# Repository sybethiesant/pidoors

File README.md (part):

# PiDoors - Open Source Access Control System

**Professional-grade physical access control powered by Raspberry Pi**

---

## Overview

PiDoors is a complete, industrial-grade access control system built on Raspberry Pi hardware. It provides enterprise-level security features while remaining affordable and open source. Designed for small businesses, makerspaces, office buildings, or anyone needing professional access control.

**Key Benefits:**
- **Cost-Effective**: 10x cheaper than commercial systems (~$100-150 per door vs $500-2000)
- **Secure**: TLS database encryption, bcrypt passwords, SQL injection protection, CSRF tokens
- **Open Source**: Full control over your security system
- **Modern Interface**: React SPA with TailwindCSS — fast, responsive single-page application
- **Offline Capable**: 24-hour local caching keeps doors working during network outages
- **Extensible**: Easy to customize and integrate

---

## Screenshots

| Dashboard | Doors |
|-----------|-------|
|  |  |

| Cards | Access Logs |
|-------|-------------|
|  |  |

| Schedules | Access Groups |
|-----------|---------------|
|  |  |

| Reports | Updates |
|---------|---------|
|  |  |

<details>
<summary>More screenshots</summary>

| Door Settings | Card Edit | Audit Log |
|---------------|-----------|-----------|
|  |  |  |

</details>

---

## Features

### Access Control
- **Multi-format Wiegand**: 26, 32, 34, 35, 36, 37, 48-bit with auto-detection
- **OSDP Readers**: RS-485 encrypted readers (planned — reader module included, not yet integrated)
- **NFC/RFID**: PN532 and MFRC522 support (planned — reader modules included, not yet integrated)
- Time-based access schedules
- Scheduled unlock — hold a door or gate open during a schedule's hours (e.g. a community gate open 6am–7pm)
- Access groups and permissions
- Holiday calendar support
- Card validity date ranges
- Persistent master cards (never expire for emergency access)
- **Master card toggle** in web UI — promote any card to master with a checkbox

### Gate Mode
- Toggle any door into **gate mode** for rolling/sliding gates with motor controllers
- 3 configurable inputs (open / stop / close physical buttons)
- 3 configurable outputs (open / stop / close relays to gate motor)
- Per-output hold duration, configurable polarity, configurable GPIO pins
- Triple-tap any button to enter hold-current-state
- Master card 3-scan = hold open (configurable)
- Stop interrupts the active output immediately
- Reverse direction commands automatically stop and reverse
- Web UI shows live gate state (idle/opening/closing/stopped/open/closed) and dedicated control buttons
- State persists across controller restarts
- Server-side pin conflict checker prevents double-assigning GPIO pins

### Reader LED
- Green / on while the door is unlocked or held open (schedule, master card or admin), red / off otherwise; a denied card blinks red
- Per-door green pin, optional red pin for bicolor readers, hi/lo polarity; defaults to the original GPIO 25 / GPIO 22 wiring
- Works on both doors and gates

### Management
- Modern React SPA with REST API backend
- Login by username or email
- Real-time dashboard with analytics
- Multi-user administration with extended profiles (name, department, company, etc.)
- Extended cardholder details (email, phone, department, employee ID, company, title)
- CSV bulk import/export with all cardholder fields (including master card flag)
- Comprehensive reporting
- Email notifications
- Complete audit trail
- Remote door control
- Instant offline detection via server-initiated polling (no stale heartbeat data)
- Door auto-registration from client heartbeat

### Updates
- One-click server updates from the web UI
- Remote controller updates via heartbeat signaling
- Pre-flight checks prevent partial updates
- Actionable error messages on failure
- Version tracking across all doors and server

### Reliability
- 24-hour offline operation
- Automatic failover
- Health monitoring
- Auto-reconnection
- Automated backups
- Service redundancy

### Security
- **TLS database encryption** — controller-to-server connections encrypted automatically
- Bcrypt password hashing (cost 12)
- PDO prepared statements (SQL injection proof)
- CSRF protection on all forms
- Secure session management
- Input validation and sanitization
- Security event logging
- Rate limiting on login

---

## Quick Start

### Prerequisites

- Raspberry Pi 3B+ or newer (Pi 4 recommended for server)
- Raspberry Pi OS (Debian-based, 64-bit recommended)
- Internet connection for initial setup
- Node.js and npm (installed automatically by `install.sh`)
- For door controllers: card reader hardware and relay module

### Automated Installation (Recommended)

```bash
# Download PiDoors
git clone https://github.com/sybethiesant/pidoors.git
cd pidoors

# Run installer as root
sudo ./install.sh
```

The installer presents three installation modes:

| Mode | Use Case |
|------|----------|
| **1) Server** | Web interface + MariaDB database (run on your central Pi) |
| **2) Door Controller** | GPIO + card reader daemon (run on each door Pi) |
| **3) Full** | Both server and controller on one Pi (small deployments) |

#### What the installer does

1. Updates system packages
2. Installs dependencies (Nginx, PHP-FPM, MariaDB, Node.js, Python libraries)
3. Generates TLS certificates and enables encrypted database connections
4. Creates the `users` and `access` databases with all required tables
5. Imports the full database schema (base tables + migration extensions)
6. Deploys the PHP API to `/var/www/pidoors/`
7. Builds the React SPA and deploys to `/var/www/pidoors-ui/`
8. Configures Nginx to serve the SPA with `/api/*` routed to PHP-FPM
9. Prompts you to create an admin account (username, email + password)
10. Sets up log rotation and backup scripts

#### After installation

1. Open `https://your-pi-ip/` in a browser
2. Log in with the email (or username `Admin`) and password you set during install
3. Navigate to **Doors** to see your door controllers as they come online
4. Navigate to **Cards** to add access cards
5. Set up **Schedules** and **Access Groups** as needed

> **Installing a door controller on a separate Pi?** The server install prints a **controller enrollment token** at the end (also stored in `/var/www/pidoors/includes/config.php` as `enrollment_token`). Enter it when the door-controller install asks for it. It lets the controller obtain a CA-signed certificate so the server can push commands to it instantly; without it the controller still works, but commands fall back to database polling.

### Manual Installation

If you prefer to install manually or need to troubleshoot:

#### 1. Install system packages
```bash
sudo apt-get update && sudo apt-get install -y \
  nginx php-fpm php-mysql php-cli php-mbstring php-curl php-json \
  mariadb-server nodejs npm \
  python3 python3-pip python3-dev python3-venv git curl
```

#### 2. Create databases
```bash
sudo mysql_secure_installation

sudo mysql -u root -p <<'SQL'
CREATE DATABASE IF NOT EXISTS users;
CREATE DATABASE IF NOT EXISTS access;
CREATE USER IF NOT EXISTS 'pidoors'@'localhost' IDENTIFIED BY 'YOUR_PASSWORD';
CREATE USER IF NOT EXISTS 'pidoors'@'%' IDENTIFIED BY 'YOUR_PASSWORD';
GRANT ALL PRIVILEGES ON users.* TO 'pidoors'@'localhost';
GRANT ALL PRIVILEGES ON access.* TO 'pidoors'@'localhost';
GRANT ALL PRIVILEGES ON users.* TO 'pidoors'@'%';
GRANT ALL PRIVILEGES ON access.* TO 'pidoors'@'%';
FLUSH PRIVILEGES;
SQL
```

> **Note:** The `'pidoors'@'%'` user allows door controllers on other Pis to connect remotely. You also need to set `bind-address = 0.0.0.0` in `/etc/mysql/mariadb.conf.d/50-server.cnf` and restart MariaDB.

#### 3. Import schemas
```bash
# Create the users table and audit_logs table in the users database
sudo mysql -u root -p users <<'SQL'
CREATE TABLE IF NOT EXISTS `users` (
  `id` int(11) NOT NULL AUTO_INCREMENT,
  `user_name` varchar(100) NOT NULL,
  `user_email` varchar(255) NOT NULL,
  `user_pass` varchar(255) NOT NULL,
  `admin` tinyint(1) NOT NULL DEFAULT 0,
  `active` tinyint(1) NOT NULL DEFAULT 1,
  `created_at` datetime DEFAULT CURRENT_TIMESTAMP,
  `last_login` datetime DEFAULT NULL,
  PRIMARY KEY (`id`),
  UNIQUE KEY `user_email` (`user_email`)
) ENGINE=InnoDB DEFAULT CHARSET=utf8mb4;

CREATE TABLE IF NOT EXISTS `audit_logs` (
  `id` int(11) NOT NULL AUTO_INCREMENT,
  `event_type` varchar(50) NOT NULL,
  `user_id` int(11) DEFAULT NULL,
  `ip_address` varchar(45) DEFAULT NULL,
  `user_agent` varchar(255) DEFAULT NULL,
  `details` text,
  `created_at` datetime NOT NULL DEFAULT CURRENT_TIMESTAMP,
  PRIMARY KEY (`id`),
  KEY `event_type` (`event_type`),
  KEY `user_id` (`user_id`),
  KEY `created_at` (`created_at`)
) ENGINE=InnoDB DEFAULT CHARSET=utf8mb4;
SQL

# Import the access database schema and migration extensions
sudo mysql -u root -p access < database_migration.sql
```

The migration script creates all access tables, adds extended columns, and also switches to the `users` database to add profile columns. It is safe to re-run on existing installations.

#### 4. Create your admin user
```bash
# Generate a bcrypt hash for your password
HASH=$(php -r "echo password_hash('YOUR_PASSWORD', PASSWORD_BCRYPT);")

sudo mysql -u root -p users -e \
  "INSERT INTO users (user_name, user_email, user_pass, admin, active) \
   VALUES ('Admin', 'admin@example.com', '$HASH', 1, 1);"
```

#### 5. Deploy the PHP API
```bash
sudo mkdir -p /var/www/pidoors
sudo cp -r pidoorserv/* /var/www/pidoors/
sudo cp VERSION /var/www/pidoors/
sudo cp /var/www/pidoors/includes/config.php.example /var/www/pidoors/includes/config.php
sudo nano /var/www/pidoors/includes/config.php    # Set your database password and server IP
sudo chown -R www-data:www-data /var/www/pidoors
sudo chmod 640 /var/www/pidoors/includes/config.php
```

#### 6. Build and deploy the React SPA
```bash
sudo apt-get install -y nodejs npm
cd pidoors-ui
npm install && npm run build
sudo mkdir -p /var/www/pidoors-ui
sudo cp -r dist/* /var/www/pidoors-ui/
sudo chown -R www-data:www-data /var/www/pidoors-ui
cd ..
```

#### 7. Configure Nginx
```bash
# Detect your PHP version
PHP_VERSION=$(php -r "echo PHP_MAJOR_VERSION.'.'.PHP_MINOR_VERSION;")

# Install config with correct PHP socket path
sudo sed "s|php-fpm.sock|php${PHP_VERSION}-fpm.sock|g" \
  nginx/pidoors.conf > /etc/nginx/sites-available/pidoors
sudo ln -sf /etc/nginx/sites-available/pidoors /etc/nginx/sites-enabled/pidoors
sudo rm -f /etc/nginx/sites-enabled/default
sudo nginx -t && sudo systemctl reload nginx
```

See the [Installation Guide](pidoors/INSTALLATION_GUIDE.md) for additional details.

---

## System Architecture

```
                    REACT SPA (Browser)
     Dashboard | Cards | Doors | Logs | Reports | Settings
                          |
                     /api/* REST
                          |
     SERVER RASPBERRY PI
    +--------------------------+
    |  Nginx                   |
    |  ├─ /         → React   |
    |  └─ /api/*    → PHP-FPM |
    |  MariaDB (TLS)           |
    |  Backups & Logs          |
    +--------------------------+
          |                  |
     HTTPS Push         TLS/TCP DB
     (instant)          (sync/poll)
          |                  |
    +----------------+  +----------------+
    |  Door Pi #1    |  |  Door Pi #N    |
    |  Push Listener |  |  Push Listener |
    |  24hr Cache    |  |  24hr Cache    |
    |  Card Reader   |  |  Card Reader   |
    |  Electric Lock |  |  Electric Lock |
    +----------------+  +----------------+
```

**One server Pi** runs the React SPA, PHP API, and database.
**N door Pis** control individual access points with 24-hour local caching.
The server pushes commands instantly via HTTPS, with database polling as fallback.
The server pings controllers on each page load for instant status. Heartbeat runs every 5 minutes as a safety net.

---

## Hardware Requirements

### Server (1 per system)
| Component | Requirement |
|-----------|-------------|
| Board | Raspberry Pi 3B+ or newer (4GB RAM recommended) |
| Storage | 16GB+ microSD card |
| Network | Ethernet recommended |
| Power | Official Raspberry Pi power supply |

### Door Controller (1 per door)
| Component | Requirement |
|-----------|-------------|
| Board | Raspberry Pi Zero W or newer |
| Storage | 8GB+ microSD card |
| Reader | See supported readers below |
| Lock | 12V electric strike or magnetic lock |
| Relay | Relay module for lock control |
| Optional | Door sensor, REX button |

**Supported Card Readers:**
| Type | Interface | Notes |
|------|-----------|-------|
| Wiegand (26/32/34/35/36/37/48-bit) | GPIO | Most common, auto-detection |
| Wiegand keypad (PIN codes) | GPIO | Burst mode or per-key (4/8-bit) mode — see *Wiegand Keypads (PIN Codes)* below |
| LCD display (HD44780) | I2C or GPIO | Optional status display at the door — see *LCD Display at the Door* below |
| OSDP v2 | RS-485 (UART) | Encrypted, requires USB-RS485 adapter — **planned, reader module not yet wired into the controller** |
| PN532 NFC | I2C or SPI | Mifare Classic, Ultralight, NTAG — **planned, reader module not yet wired into the controller** |
| MFRC522 NFC | SPI | Low-cost Mifare reader |

**Total cost per door: ~$100-150**

---

## Configuration

### Server Configuration

1. Copy the configuration template:
```bash
cp pidoorserv/includes/config.php.example pidoorserv/includes/config.php
```

2. Edit configuration:
```bash
nano pidoorserv/includes/config.php
```

3. Set your values:
```php
return [
    'sqladdr' => '127.0.0.1',
    'sqldb' => 'users',
    'sqldb2' => 'access',
    'sqluser' => 'pidoors',
    'sqlpass' => 'your_secure_password',
    'url' => 'https://your-pi-ip',
    // ... other settings
];
```

4. Secure the file:
```bash
chmod 640 pidoorserv/includes/config.php
```

### Door Controller Configuration

1. Copy the configuration template:
```bash
cp pidoors/conf/config.json.example pidoors/conf/config.json
```

2. Edit configuration:
```bash
nano pidoors/conf/config.json
```

3. Set your values (use your actual door name as the key):
```json
{
    "frontdoor": {
        "reader_type": "wiegand",
        "d0": 24,
        "d1": 23,
        "wiegand_format": "auto",
        "latch_gpio": 18,
        "open_delay": 5,
        "unlock_value": 1,
        "sqladdr": "SERVER_IP_ADDRESS",
        "sqluser": "pidoors",
        "sqlpass": "your_database_password",
        "sqldb": "access"
    }
}
```

---

## Wiring Guide

### Wiegand Reader to Raspberry Pi

**Important:** Most Wiegand readers output 5V logic signals, but Raspberry Pi GPIO pins are 3.3V only. A **bi-directional logic level shifter** (5V to 3.3V) is recommended on the DATA0 and DATA1 lines to protect the Pi's GPIO pins. Without one, the Pi may work initially but the GPIO pins can be damaged over time.

| Wiegand Reader | Level Shifter | Raspberry Pi |
|----------------|---------------|--------------|
| DATA0 (Green)  | HV1 → LV1    | GPIO 24      |
| DATA1 (White)  | HV2 → LV2    | GPIO 23      |
| GND (Black)    | GND (shared)  | GND (Pin 6)  |
| 5V+ (Red)      | HV            | 5V (Pin 2)   |
| —              | LV            | 3V3 (Pin 1)  |

### Lock Relay Control

| Relay Module | Raspberry Pi |
|--------------|--------------|
| IN           | GPIO 18      |
| VCC          | 5V (Pin 4)   |
| GND          | GND (Pin 14) |

Connect lock to relay NO/COM terminals with 12V power supply.

### Gate Mode Wiring (Optional)

For rolling/sliding gates with motor controllers, enable **Gate Mode** in the door edit page. Each gate has up to 3 inputs (physical buttons) and 3 outputs (relays to the gate motor). All inputs and outputs are optional — only enable the ones your hardware supports. GPIO pins are assigned in the web UI from the available pin list.

**Gate Outputs (relays to motor)** — typically wire each relay's NO/COM terminals to the corresponding input on your gate motor controller (open, stop, close terminals).

| Gate Output | Purpose |
|-------------|---------|
| Open relay  | Held active for the configured duration to open the gate |
| Close relay | Held active for the configured duration to close the gate |
| Stop relay  | Optional — fires when stop is triggered, for motor controllers with a dedicated stop input |

**Gate Inputs (physical buttons or RF remote relays)** — wire the button/relay between the assigned GPIO pin and GND (default pull-up mode).

| Gate Input  | Purpose |
|-------------|---------|
| Open button | Triggers the open output (3-tap = hold open) |
| Close button | Triggers the close output (3-tap = hold closed) |
| Stop button | Cuts the active output immediately (3-tap = hold at current position) |

**Voltage Warning:** Same as Wiegand readers — if your buttons or RF remote relays output 5V signals, use a level shifter to protect the Pi's 3.3V GPIO inputs. For dry-contact switches (relay closures to ground) no level shifter is needed.

In gate mode, the regular **Lock Relay** is unused — the gate's open/close outputs replace it. The "Unlock Duration" field in the door edit page is automatically hidden when gate mode is enabled. Each gate output has its own configurable hold duration.

### LED Feedback

The reader LED follows the state of the door, so members can see whether it is open right now:

| Door state | Green line | Red line (if wired) |
|------------|------------|---------------------|
| Locked / idle | Off | On |
| Unlocked by a card, held open by a **schedule**, master card or admin, gate open cycle or gate held | On | Off |
| Card denied while locked | Off (single-line readers blink it on) | Blinks dark |
| Card denied while open | Blinks off | Blinks on (shows red) |

Configure it in the **Reader LED** section of the door edit page; changes take effect on the next config push, no restart needed.

- **LED pin (green / open)** — the line that is lit while the door is open. For readers with a single LED control input (most HID / Wiegand readers, where pulling the line low turns the LED green) this is the only pin you need; set **Active** to *Low* for those.
- **Red pin (optional)** — a second line for keypads with separate red and green inputs, or a two-wire bicolor LED. It is driven as the inverse of the green line.
- **Active** — high (3.3V) or low (GND) for both lines.

A door that has never had its LED configured uses the original wiring, GPIO 25 green and GPIO 22 red, active high, and that is what the form shows preselected. Untick **Reader LED** to stop driving those pins, which frees them for gate I/O, an LCD or a reader that needs them (the MFRC522 reset line, for example). All LED pins go through the same pin-conflict checks as everything else on the door.

### LCD Display at the Door

An optional character LCD (the common HD44780 type: 16x2, 20x4, etc.) can be attached to the controller to show what is happening at the door. Enable **LCD display** on the door edit page; the controller picks the change up on the next config push, no restart needed.

What it shows:
- **Idle**: the door name on line 1; `Ready`, `Held open`, `Gate held` or `LOCKDOWN` plus the time on line 2.
- **Access granted** with the cardholder's name, or **Access denied** with the reason, for 3 seconds.
- **Enter code** with one `*` per digit while a PIN is typed on a per-key keypad.

Two wiring types are supported. Pins are assigned in the web UI and checked against everything else on the door (reader, lock, sensor, gate I/O, status LED).

| Wiring | Config | Notes |
|--------|--------|-------|
| **I2C backpack** (PCF8574 piggyback board, 4 wires) | Address (usually `0x27` or `0x3F`), bus (1) | Uses GPIO 2 (SDA) / GPIO 3 (SCL). Enable I2C once on the controller: `sudo raspi-config nonint do_i2c 0`, and make sure the service user can use the bus: `sudo usermod -aG i2c pidoors` (fresh installs do this for you). Find the address with `i2cdetect -y 1`. |
| **GPIO wired** (HD44780 in 4-bit mode) | RS, E, D4, D5, D6, D7, optional backlight pin | Tie RW to GND, D0–D3 unconnected, contrast pot on V0. Any free GPIO pins. |

Most 5V LCDs run happily with 3.3V logic on the data lines; power the panel from 5V. The display is best-effort: if it fails to initialise the controller logs `LCD setup failed` and carries on without it.

### Wiegand Keypads (PIN Codes)

A Wiegand keypad works with PiDoors today with no extra configuration. The controller does not distinguish a code typed on a keypad from a card presented to a reader: both arrive as a Wiegand frame, and a PIN is enrolled and managed exactly like a card. This also makes PiDoors usable for machine or equipment access (see the end of this section).

**What you need**

- Any keypad, or combined reader/keypad, with a Wiegand output. Both output modes work:
  - **Buffered / burst / "card format" mode**: the user types the digits and presses `#` (or waits for the keypad's timeout), and the keypad sends the whole code as **one** 26-bit (or 34/37-bit) frame. The controller decodes it like a card.
  - **Per-key mode** (4-bit or 8-bit "one frame per keypress"): the keypad sends each key as it is pressed. The controller collects the digits itself; `#` submits, `*` clears, and a pause of more than 5 seconds between keys discards a half-typed code. The digits are packed into the same 26-bit (or 34-bit for codes above 16,777,215) frame a burst-mode keypad would send, so a code enrolled on one kind of keypad matches on the other. Per-reader settings in `config.json`: `pin_timeout` (seconds, default 5) and `pin_max_length` (digits, default 10).
  - Most inexpensive keypads support both and default to per-key; the mode is a DIP switch or programming-code option in the keypad's manual (look for "Wiegand output format"). It no longer matters which one you pick.
- Wire DATA0 / DATA1 exactly like a card reader (see *Wiegand Reader to Raspberry Pi* above), including the 5V → 3.3V level shifter. The keypad's LED control line can go to GPIO 22 (see *LED Feedback*) so it turns green on a valid code.
- Nothing to change on the controller or in `config.json`. The frame is decoded by the same format registry (26/32/34/35/36/37/48-bit, parity checked).

**What does not work**

- **Card + PIN (two-factor).** The `pin_code` column on cards is stored, imported and exported, but the controller does not enforce it. A PIN is a standalone credential.
- **Non-Wiegand keypads**: matrix keypads on GPIO, I²C expanders such as the PCF8574, USB keypads. These would need a new reader module under `pidoors/readers/`. The `BaseReader` interface is there, but only the Wiegand reader is wired into the controller today; the OSDP and NFC modules are also not yet integrated.

**How a PIN becomes a credential**

- The keypad packs the digits into the frame's data bits. The controller validates parity, then splits the frame into *facility* + *user ID* by frame length (26-bit: 8 + 16 bits; 34-bit: 16 + 16; 37-bit: 16 + 19). A 6-digit code on a 26-bit keypad therefore usually shows up as a non-zero facility with a 5-digit user ID. That is expected: what matters is that the same code always produces the same pair.
- Code length is limited by the frame's data bits, not by a digit count: a 26-bit frame carries 24 data bits (codes up to 16,777,215, i.e. 8 digits), 34-bit carries 32. Some keypads impose their own maximum; check the manual.
- Leading zeros are not preserved: `000123` and `123` are the same credential.

**Enrolling a code**

1. Type the code on the keypad and press `#`.
2. The controller denies it as unknown, inserts it into the database as an **inactive** card, and logs the attempt (the controller must be able to reach the database for this; offline it just denies).
3. In the web UI open **Logs**, find the denied entry, and click **Set Up Card**. Give it a name, doors, group/schedule, and set it active.
4. Type the code again. Access is granted.

The same flow works for new cards, so a keypad or reader at any door doubles as an enrollment station. There is no need for a reader at the server.

**Machine / equipment access.** To gate a machine rather than a door, drive a latching relay or contactor that powers the machine from the lock relay output. Set the door's **Unlock Duration** to how long the machine should stay enabled after a valid code (up to the `max_unlock_duration` setting), use a master-card hold (3 scans) to keep it enabled indefinitely, or assign an **Unlock Schedule** to keep it powered during set hours.

### GPIO Pin Reference
```
    3V3  (1)  (2)  5V
  GPIO2  (3)  (4)  5V
  GPIO3  (5)  (6)  GND
  GPIO4  (7)  (8)  GPIO14
    GND  (9)  (10) GPIO15
 GPIO17 (11) (12) GPIO18    <- Relay (GPIO18)
 GPIO27 (13) (14) GND
 GPIO22 (15) (16) GPIO23    <- DATA1 (GPIO23)
    3V3 (17) (18) GPIO24    <- DATA0 (GPIO24)
 GPIO25 <- Green LED (legacy)
 GPIO22 <- Red LED (legacy)
```

Full wiring diagrams available in [Installation Guide](pidoors/INSTALLATION_GUIDE.md#wiring).

---

## Usage

### Adding a Card

**Via Web Interface:**
1. Navigate to **Cards** > **Add Card**
2. Enter card details (scan card at reader to get ID)
3. Assign access groups and schedules
4. Click **Add Card**

**Via a reader or keypad (auto-enrollment):**
1. Present the card (or type the PIN and press `#`) at any door. The attempt is denied and the credential is saved as an inactive card.
2. Open **Logs**, find the denied entry, click **Set Up Card**, fill in the details and set it active.

**Via CSV Import:**
```csv
card_id,user_id,firstname,lastname,email,department
12345678,EMP001,John,Smith,john@example.com,Engineering
87654321,EMP002,Jane,Doe,jane@example.com,Marketing
```

Upload at **Cards** > **Import CSV**. Optional columns: `email`, `phone`, `department`, `employee_id`, `company`, `title`, `notes`, `group_id`, `schedule_id`, `valid_from`, `valid_until`, `pin_code` (stored only; card + PIN is not enforced by the controller, see *Wiegand Keypads (PIN Codes)*).

### Creating Access Schedules

1. Go to **Schedules** > **Add Schedule**
2. Name the schedule (e.g., "Business Hours")
3. Add one or more **time windows**. Each window has a set of days (tap to toggle Mon–Sun) and a start/end time; a day can appear in as many windows as you need, and an end earlier than the start runs past midnight. For example, a gate that opens every day 11:30–13:10, Mon–Fri 16:45–18:30 and Sat–Sun 07:30–09:15 is three windows on one schedule.
4. Assign to cards (restricts when the card works) or to doors (see below)

### Access Groups

An access group carries a list of doors. A card assigned to a group is granted every door in the group's list **in addition to** the doors on the card itself, so you can manage door sets centrally and leave most cards' own door list empty. Notes:

- The group must list doors explicitly. A group with no doors selected grants nothing extra (it is just a label), and it never restricts a card's own doors.
- Schedules, validity dates, holidays and scan limits still come from the card.
- Controllers pick up group changes on their next cache sync (hourly, or immediately on a config push).

### Scheduled Unlock (Hold Open by Schedule)

To keep a door or gate open during set hours — a community gate open 6am–7pm, a lobby door unlocked during business hours — assign a schedule to the **door** in **Doors** > edit > **Unlock Schedule**.

- When the schedule window opens, the controller enters the held-open state (latch energized, or gate opened and held). When it closes, the door relocks (or the gate is released and closed).
- The controller evaluates the schedule every 15 seconds and acts on the transitions, so a master card or an admin can still release a hold mid-window; the schedule will not fight that release and re-applies on the next window start.
- A controller that reboots mid-window re-applies the hold. Clearing the door's schedule releases a hold the schedule applied.
- **Lockdown mode** and **access-denied holidays** override the schedule — a door that is locked down or closed for a holiday is never propped open.
- A schedule can have several windows a day (v0.4.9+); the door is held open during each one and relocks in the gaps between them.
- Overnight windows (e.g. 22:00 → 06:00) are supported. Master-card and admin holds placed *before* the window opens are left alone at window end.
- Card access is unaffected: outside the window the door works normally for authorized cards. Leave the door schedule at **None** for a door that should only ever open on a valid card.

### Monitoring Access

- **Dashboard**: Real-time statistics and charts
- **Access Logs**: Filter by date, door, user; export to CSV
- **Audit Log**: Track all administrative actions
- **Email Alerts**: Failed access attempts, door offline notifications

---

## Maintenance

### Automatic Backups
Backups run daily at 2 AM to `/var/backups/pidoors/` (database dumps plus the web root). Retention follows the **Backup retention (days)** value on the Settings page, default 30. The dump credentials live in the root-only file `/etc/pidoors/backup.cnf`.

### Manual Backup
```bash
sudo /usr/local/bin/pidoors-backup.sh
```

### Update PiDoors

**Via Web UI (Recommended):**
1. Go to **Updates** in the admin sidebar
2. Click **Check for Updates** to see the latest release
3. Click **Update Server** to update the web interface
4. Use the **Doors** page to push updates to door controllers

**Manual update:**
```bash
cd ~/pidoors
git pull
sudo cp -r pidoorserv/* /var/www/pidoors/
sudo systemctl restart nginx
sudo systemctl restart pidoors  # On door controllers
```

### Database Migrations

Both the in-app updater and `server-update.sh` apply `database_migration.sql` automatically through the root helper `/usr/local/sbin/pidoors-db-migrate` (v0.4.7+). If an update reports that the migration failed, fix the reported error and run:

```bash
sudo /usr/local/sbin/pidoors-db-migrate
```

If the helper is missing (installs made before v0.4.7 that have only ever updated through the web UI), run `sudo bash server-update.sh` once from the extracted release; it installs the helper and applies any missed migrations.

To run the migration by hand instead:

```bash
# Backup first
mysqldump -u pidoors -p access > backup_access_$(date +%Y%m%d).sql
mysqldump -u pidoors -p users > backup_users_$(date +%Y%m%d).sql

# Run migration (safe to re-run, uses IF NOT EXISTS checks)
mysql -u root -p access < database_migration.sql
```

The migration script handles both the `access` and `users` databases automatically.

**v2.2.1 Migration (Required if upgrading from v2.2 or earlier):**

This migration converts door assignments from space-separated to comma-separated format:

```bash
python3 migrations/migrate_doors_format.py --dry-run   # Preview
python3 migrations/migrate_doors_format.py              # Apply
```

### View Logs
```bash
# Door controller logs
sudo journalctl -u pidoors -f

# Web server logs
sudo tail -f /var/log/nginx/pidoors_error.log
```

---

## Security

### Security Features
- TLS encryption for all database connections (auto-configured during install)
- Bcrypt password hashing with automatic MD5 upgrade
- PDO prepared statements (no SQL injection)
- CSRF token protection on all forms
- Secure session handling with timeout
- Comprehensive input validation
- Complete audit logging
- Login rate limiting (5 attempts, 15-minute lockout)

### Reporting Vulnerabilities
Please report security issues to the repository owner directly, not via public issues.

---

## File Structure

```
pidoors/
├── pidoorserv/           # PHP API backend
│   ├── api.php           # Unified REST API router
│   ├── includes/         # Core PHP includes
│   │   ├── config.php.example
│   │   ├── security.php
│   │   ├── header.php
│   │   ├── push.php      # Push communication & status polling
│   │   ├── notifications.php
│   │   └── smtp.php      # Lightweight SMTP sender
│   ├── cron/             # Scheduled tasks (notifications)
│   ├── users/            # User management
│   ├── database/         # Database connection
│   ├── css/              # Stylesheets (legacy)
│   └── js/               # JavaScript (legacy)
├── pidoors-ui/           # React SPA frontend
│   ├── src/
│   │   ├── pages/        # Dashboard, Cards, Doors, Settings, etc.
│   │   ├── components/   # Shared UI components
│   │   ├── contexts/     # Auth context
│   │   ├── api/          # REST API client
│   │   └── types/        # TypeScript type definitions
│   ├── package.json
│   └── vite.config.ts
├── pidoors/              # Door controller
│   ├── pidoors.py        # Main daemon
│   ├── pidoors.service   # Systemd service
│   ├── pidoors-update.sh # Self-update script (runs as root via sudo)
│   ├── readers/          # Card reader modules
│   │   ├── base.py       # Abstract base class
│   │   ├── wiegand.py    # Wiegand GPIO reader
│   │   ├── osdp.py       # OSDP RS-485 reader
│   │   ├── nfc_pn532.py  # PN532 NFC reader
│   │   └── nfc_mfrc522.py # MFRC522 NFC reader
│   ├── formats/          # Card format definitions
│   │   └── wiegand_formats.py
│   └── conf/             # Configuration
│       └── config.json.example
├── nginx/                # Nginx configuration
│   └── pidoors.conf
├── docker/               # Docker dev/test environment
│   ├── docker-compose.yml
│   ├── Dockerfile.server
│   ├── Dockerfile.door
│   ├── server-entrypoint.sh
│   ├── door-entrypoint.sh
│   ├── deploy.sh         # Deploy to remote Docker host
│   └── mock_gpio.py      # Mock GPIO for containerized door
├── VERSION               # Current version number
├── install.sh            # Installation script
├── server-update.sh      # Server self-update script
├── database_migration.sql
└── README.md
```

---

## Documentation

| Document | Description |
|----------|-------------|
| [Installation Guide](pidoors/INSTALLATION_GUIDE.md) | Complete beginner-friendly setup |

---

## Contributing

Contributions welcome! Please:

1. Fork the repository
2. Create a feature branch (`git checkout -b feature/amazing-feature`)
3. Commit your changes (`git commit -m 'Add amazing feature'`)
4. Push to the branch (`git push origin feature/amazing-feature`)
5. Open a Pull Request

**Requirements:**
- Test on actual Raspberry Pi hardware
- Verify database migrations work
- Check security implications
- Update documentation

---

## Roadmap

**Current Version: 0.4.11** - Pre-release

**Future Enhancements** (community contributions welcome):
- Mobile app (iOS/Android)
- Bluetooth Low Energy (BLE) readers
- Biometric integration (fingerprint, face)
- Cloud backup integration
- Multi-site management dashboard

---

## Changelog

> **Note:** Version numbering was reset from 3.x to 0.x in April 2026. The project had rapidly iterated from v1.0 to v3.2 during initial development. The 0.x series reflects pre-release status as the system matures toward a proper v1.0.0 release.

### Version 0.4.11 (September 2026)
- **Reader LED stays green for as long as the door is open — fixes #8.** The configurable status LED (any GPIO pin) only pulsed for two seconds on a granted scan; during a scheduled unlock, a master-card or admin hold, or even the rest of a normal five-second unlock it went dark, although the feature list had claimed it lit "during hold states" since 0.3.3. Only the hardcoded GPIO 25 line did that. The LED now follows the door: on / green while the latch is energised or the door or gate is held, off / red otherwise, and scan animations settle back to the real state instead of switching a held-open LED off.
  - **Denied card while the door is open blinks red** (single-line LED blinks off) so a refused card is visible against the steady green. At idle a bicolor pair still blinks its red dark and a single-line LED blinks on.
  - **The old hardcoded GPIO 22 / 25 LEDs are now the default of the same configurable feature** instead of a separate always-on code path. The door edit page's **Reader LED** section has a green pin, an optional red pin and the polarity, preselected to GPIO 25 / GPIO 22 for doors that never configured an LED. Those pins finally take part in the pin-conflict checker, so a gate relay, LCD line or reader that needs GPIO 22 or 25 is reported instead of being silently fought by the LED code; untick **Reader LED** or move it to free them.
  - Existing single-pin status LED configs carry over as the green line with no red line. Doors that had such a config *and* relied on the hardcoded pair being driven as well should add GPIO 22 as the red pin, or move the green line to GPIO 25.
  - Gate mode: the LED goes green for every open cycle and while the gate is held, not only for card-triggered opens.

### Version 0.4.10 (September 2026)
- **Schedule, holiday, card, group, door and settings changes reach online doors immediately — fixes #7.** Controllers cache this data and only re-read it from the database once an hour, and the server only pushed a reload for gate/LED/LCD config changes. Assigning an **Unlock Schedule** to a door, or editing the schedule's hours, therefore did nothing until the next hourly sync (or a controller restart). The API now pushes a cache sync to every reachable controller after any such change, in parallel and after the HTTP response is sent, so the UI is never held up by a slow door. Doors that are offline still catch up on their next sync.
  - The controller re-evaluates its unlock schedule right after each sync, so a window that is already open is applied within a second instead of at the next 15 s tick. Concurrent syncs (hourly vs. pushed) are serialized.
  - Card swipes were never affected while online: the controller checks the database live for those and only uses its cache when the server is unreachable.

### Version 0.4.9 (September 2026)
- **Schedules can have more than one time window per day — fixes #6.** A schedule used to hold a single start/end per weekday, so "open 11:30–13:10 and again 19:25–21:10 every day, plus 16:45–18:30 on weekdays" could not be expressed. Schedules are now a list of windows, each with its own set of days and start/end time, with no limit on how many windows share a day. This applies to both card access schedules and door **Unlock Schedules**.
  - New `schedule_windows` table. The migration seeds it from the existing per-day columns, so current schedules carry over unchanged.
  - The legacy per-day columns are kept and always mirror each day's *first* window, so a controller still on an older release keeps enforcing a reduced version of the schedule until it is updated. Update controllers to 0.4.9 to get every window.
  - Schedules page redesigned around the window list (day toggles + start/end per row). Older API clients that still send the per-day fields keep working.

### Version 0.4.8 (September 2026)
- **`server-update.sh` failed at "Release archive missing pidoorserv/ directory".** Its temp directory is named `pidoors-server-update-…`, and the search for the extracted `pidoors-*` folder matched the temp directory itself. The CLI updater had been broken since that temp-dir naming was introduced; the in-app updater was unaffected. This matters now because v0.4.7 tells existing installs to run it once. Also: the migration helper no longer echoes the migration's placeholder `SELECT 1` rows.

### Version 0.4.7 (September 2026)
- **Database migrations now actually run on upgrades.** Since the v0.4.0 hardening the app DB user has had no CREATE/ALTER, so the migration step in both the in-app updater and `server-update.sh` failed on its first statement and was reported as a *warning*. Every schema change shipped since then was silently skipped on upgraded installs (fresh installs were fine). v0.4.6 was the first release to add a column (`lcd_config`), which made this visible: saving a door's LCD config failed with an unknown-column error.
  - New root helper `/usr/local/sbin/pidoors-db-migrate` runs the deployed migration as a dedicated `pidoors_migrate` DB user (DDL on the two PiDoors databases only, credentials in root-only `/etc/pidoors/migrate.cnf`). The web updater calls it via sudoers, the same way as the nginx helper.
  - A failed migration is now an **error** in the UI and a non-zero exit from `server-update.sh`, with the command to fix it.
  - **Existing installs:** run `sudo bash server-update.sh` once (from the extracted release or a clone). It installs the helper and the DB user, asking for the MariaDB root password only if root needs one, and applies any missed migrations. After that, in-app updates handle schema changes on their own.

### Version 0.4.6 (September 2026)
- **Per-key Wiegand keypads now work.** Keypads in 4-bit or 8-bit "one frame per keypress" mode were ignored (`Unsupported Wiegand format`). The controller now collects the keys itself (`#` submits, `*` clears, 5 s inter-key timeout) and packs the digits into the same 26/34-bit frame a burst-mode keypad sends, so the same code enrolls and matches on either kind. Per-reader `pin_timeout` / `pin_max_length` in `config.json`. Closes the remaining question on issue #4.
- **LCD display at the door.** Optional HD44780 character LCD, either on a PCF8574 I2C backpack or wired to GPIO in 4-bit mode, configured per door in the web UI with pin-conflict checking. Shows door name and hold/lockdown state at idle, granted/denied with name or reason, and PIN entry progress. New `lcd_config` column on `doors`, new `pidoors/lcd.py` on the controller. See *LCD Display at the Door*.

### Version 0.4.5 (September 2026)
**Audit fixes.** A sweep of the controller, API, SPA and installer for features that were exposed but not wired up. Everything below was broken or inert before this release.

Controller
- **Access groups now grant access.** The controller never read `access_groups`, so a group's door list was a label. Cards whose group lists the door are now included in the door's cache and pass the online check. Groups must name doors explicitly; an empty group grants nothing (conservative on upgrade). See *Access Groups* under Usage.
- **Schedules starting at 00:00 denied access on the offline path** — the cached check used falsiness and PyMySQL returns midnight as `timedelta(0)`. Now `is None`, matching the DB path.
- **Recurring holidays with a past date never reached the offline cache** (`date >= CURDATE()` dropped them). Recurring rows are always synced.
- **Global settings were dropped from the cache file** because it was saved before they were attached. Saved after.
- **Lockdown mode is read on the fast command poll**, so it takes effect within seconds instead of on the hourly sync.
- Docstring no longer claims OSDP/NFC support; the reader-type dropdown marks those options as planned and disabled.

Server / web UI
- **Controller certificate enrollment could never succeed.** `/api/certs/sign` refused unless `enrollment_token` was set in config.php, and nothing ever set or sent it — every controller fell back to a self-signed cert the server's CA pin then rejected, so push commands silently degraded to polling. The server install now generates the token (printed in the summary), the door install prompts for it, and all three signing callers send it. Existing installs: set `enrollment_token` in config.php, add it to the controller's `config.json`, and re-run `pidoors-update.sh` to re-sign.
- **In-app server update now verifies the published `.sha256`** before extracting and no longer falls back to the GitHub source archive (which skipped verification and contained no built SPA). Matches `server-update.sh`.
- **"Send Test Email" always failed** — it called a function that did not exist. Uses the SMTP sender.
- **Cards created in the UI could not be edited or deleted** until first scanned (the API keys on `card_id`, which is NULL until then). They can now be addressed by primary key.
- **Creating a door dropped its gate, status-LED and lockdown settings** — only the edit path saved them. The create path persists and validates them too; a door named `all` is rejected (it collides with the update-all route).
- **Security settings were inert.** Login lockout attempts/duration and password rules edited on the Settings page are now applied (they were read from config.php only).
- Notification emails link to the SPA routes instead of the retired `.php` pages.
- Schedules, Access Groups and Holidays are hidden from non-admins instead of loading and failing with 403.
- Update page compares versions numerically (string compare broke past `0.4.9`).

Installer
- **Automatic backup is actually scheduled** (daily 02:00). It was installed but never added to cron. Retention now follows the Settings page value, and the DB password moved from a command-line argument to a root-only credentials file.
- The `nginx/` template is copied into the web root so the nginx upgrade helper has a source after a fresh install.

Not changed (known, documented): `pin_code` and anti-passback columns are stored but unused; several Settings keys (`maintenance_mode`, `log_retention_days`, `cache_duration`, `default_*`) are saved but read by nothing; legacy PHP pages are still shipped though unreachable behind the SPA nginx config.

### Version 0.4.4 (September 2026)
**Scheduled unlock (hold open by schedule) — fixes #5.** The **Schedule** dropdown on the door edit page has existed since the schedules feature landed, but the controller never read `doors.schedule_id` — the field was saved and then ignored, so "hold the gate open 6am–7pm" silently did nothing. The controller now runs an unlock-schedule thread that holds the door (or opens and holds the gate) when the assigned schedule's window opens and releases it when the window closes. It is edge-triggered, so master-card / admin releases mid-window are respected; it re-applies after a reboot mid-window; and lockdown mode or an access-denied holiday overrides it. The field is now labeled **Unlock Schedule** in both UIs with the behavior spelled out. See *Scheduled Unlock* under Usage.

**Dependency security updates** — React SPA toolchain, `npm audit`: 0 vulnerabilities. Both are build-time (dev) dependencies; neither ships in the deployed bundle or is reachable from the web UI.
- `browserslist` 4.28.2 → 4.28.9 — uncaught crash / prototype write via untrusted `browserslist-stats.json` custom stats in `normalizeStats` ([GHSA-73wf-gq98-2v4g](https://github.com/advisories/GHSA-73wf-gq98-2v4g), CVE-2026-73088).
- `postcss-selector-parser` 6.1.2 → 6.1.4 — denial of service through uncontrolled AST recursion ([GHSA-w9m9-85wc-3x92](https://github.com/advisories/GHSA-w9m9-85wc-3x92), CVE-2026-9358).

### Version 0.4.3 (August 2026)
**Dependency security updates** — clears every open advisory in the React SPA toolchain (`npm audit`: 0 vulnerabilities). No application code changed; the pre-built SPA bundle was rebuilt against the patched dependencies.
- `postcss` 8.5.15 → 8.5.26 — fixes a path traversal in source-map auto-loading, where a crafted `sourceMappingURL` comment could disclose arbitrary `.map` files ([GHSA-r28c-9q8g-f849](https://github.com/advisories/GHSA-r28c-9q8g-f849)).
- `react-router` / `react-router-dom` 6.30.4 → 7.18.2 — the open redirect leading to XSS ([GHSA-jjmj-jmhj-qwj2](https://github.com/advisories/GHSA-jjmj-jmhj-qwj2)) has no patch on the 6.x line, so this required the 6 → 7 major upgrade. That also picks up arbitrary constructor injection via `deserializeErrors()` in SSR hydration ([GHSA-337j-9hxr-rhxg](https://github.com/advisories/GHSA-337j-9hxr-rhxg)) and an open redirect via backslash in `<Link>` / `useNavigate` ([GHSA-wrjc-x8rr-h8h6](https://github.com/advisories/GHSA-wrjc-x8rr-h8h6)).

The router major needed no source changes: the UI uses only `BrowserRouter`, `Routes`, `Route`, `Navigate`, `Outlet`, `Link`, `NavLink`, `useSearchParams` and `useNavigate` — all unchanged in v7 — and has no data-router loaders/actions, `<Form>`, or splat-relative links.

### Version 0.4.2 (June 2026)
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
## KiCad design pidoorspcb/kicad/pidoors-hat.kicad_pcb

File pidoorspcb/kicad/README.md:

# PiDoors HAT KiCad Project

KiCad 8 project files for the PiDoors Access Control HAT.

## Project Files

| File | Description | Status |
|------|-------------|--------|
| `pidoors-hat.kicad_pro` | KiCad project file | Complete |
| `pidoors-hat.kicad_sch` | Schematic with all components | Complete |
| `pidoors-hat.kicad_pcb` | PCB layout (needs routing) | Outline Only |
| `pidoors-hat.net` | Complete netlist | Complete |
| `pidoors-hat-bom.csv` | Bill of Materials with LCSC parts | Complete |
| `pidoors-hat-cpl.csv` | Component Placement List | Complete |

## Current Status

This project provides:
- **Complete schematic** with all 50+ components placed
- **Complete netlist** with all connections defined
- Pi HAT board outline (65mm x 56.5mm)
- Mounting hole positions (M2.5)
- BOM with LCSC part numbers for JLCPCB assembly

**To complete the design for manufacturing:**
1. Open in KiCad 8: `kicad pidoors-hat.kicad_pro`
2. Update PCB from Schematic (Tools menu)
3. Place component footprints per the placement guide
4. Route traces
5. Run DRC (Design Rule Check)
6. Generate Gerber files

## Quick Start - Complete the Design

### Option 1: Use KiCad (Recommended for Customization)

1. **Open the project in KiCad 7 or 8**
   ```bash
   kicad pidoors-hat.kicad_pro
   ```

2. **Create schematic from netlist**
   - Open Eeschema (schematic editor)
   - Add symbols from KiCad standard libraries
   - Connect according to netlist

3. **Import netlist to PCB**
   - Open PCBnew
   - Tools → Update PCB from Schematic
   - Place components within board outline
   - Route traces

4. **Generate manufacturing files**
   - File → Fabrication Outputs → Gerbers
   - File → Fabrication Outputs → Drill Files

### Option 2: Use EasyEDA (Easiest for JLCPCB Orders)

1. Go to [EasyEDA](https://easyeda.com)
2. Create new project
3. Use the netlist as reference to create schematic
4. Convert to PCB, place components
5. Order directly from JLCPCB with one click

### Option 3: Hire a Designer

Give the following files to a PCB designer on Fiverr/Upwork:
- `pidoors-hat.net` - Complete netlist
- `../PCB_SPECIFICATION.md` - Full design specification
- This README

Estimated cost: $50-150 for complete design with Gerbers.

## Component Placement Guide

```
┌─────────────────────────────────────────────────────────────────┐
│ H1                                                          H2 │
│ (3.5,3.5)                                            (61.5,3.5)│
│                                                                 │
│    J2          U1        U2                                    │
│  Barrel     DC-DC      LDO         C1   C2                     │
│   Jack      5V        3.3V                                     │
│  (5,12)   (15,12)   (25,12)     (35,10) (40,10)               │
│                                                                 │
│  ┌──────────────────────────────────────────────────────┐      │
│  │                                                      │      │
│  │              J1 - Raspberry Pi GPIO                  │      │
│  │                   2x20 Header                        │      │
│  │                  (7.5 to 57.5, 25)                   │      │
│  │                                                      │      │
│  └──────────────────────────────────────────────────────┘      │
│                                                                 │
│  J3         J4          J5        J6         D8-D11            │
│ Wiegand   RS-485      PN532     NFC SPI      LEDs              │
│ (8,42)   (20,42)     (32,42)   (44,42)     (55,42)            │
│                                                                 │
│  J7         J8        J9        J10       J11                  │
│ Relay    DoorSns     REX      Tamper    Buzzer                 │
│ (8,50)   (18,50)   (28,50)   (38,50)   (48,50)                │
│                                                                 │
│ H3                                                          H4 │
│ (3.5,53)                                              (61.5,53)│
└─────────────────────────────────────────────────────────────────┘
```

## Footprint Assignments

| Ref | Footprint | Notes |
|-----|-----------|-------|
| J1 | `Connector_PinSocket_2.54mm:PinSocket_2x20_P2.54mm_Vertical` | Pi GPIO |
| J2 | `Connector_BarrelJack:BarrelJack_CUI_PJ-002A_Horizontal` | 5.5x2.1mm |
| J3,J4 | `TerminalBlock_Phoenix:TerminalBlock_Phoenix_MKDS-1,5-4-5.08_1x04_P5.08mm_Horizontal` | 4-pos screw |
| J5 | `Connector_PinHeader_2.54mm:PinHeader_1x06_P2.54mm_Vertical` | 6-pin |
| J6 | `Connector_PinHeader_2.54mm:PinHeader_1x08_P2.54mm_Vertical` | 8-pin |
| J7 | `TerminalBlock_Phoenix:TerminalBlock_Phoenix_MKDS-1,5-3-5.08_1x03_P5.08mm_Horizontal` | 3-pos |
| J8,J9,J11 | `TerminalBlock_Phoenix:TerminalBlock_Phoenix_MKDS-1,5-2-5.08_1x02_P5.08mm_Horizontal` | 2-pos |
| J10 | `Connector_PinHeader_2.54mm:PinHeader_1x02_P2.54mm_Vertical` | 2-pin |
| U1 | `Converter_DCDC:Converter_DCDC_muRata_OKI-78SRx_Vertical` | DC-DC |
| U2 | `Package_TO_SOT_SMD:SOT-223-3_TabPin2` | LDO |
| U3 | `Package_SO:SOIC-8_3.9x4.9mm_P1.27mm` | RS-485 |
| U4 | `Package_TO_SOT_SMD:SOT-23-6` | Level shifter |
| U5 | `Package_DIP:DIP-4_W7.62mm` | Optocoupler |
| K1 | `Relay_THT:Relay_SPDT_Omron-G5LE-14` | Relay |
| Q1 | `Package_TO_SOT_SMD:SOT-23` | NPN |
| D1 | `Diode_SMD:D_SMB` | TVS |
| D2-D5 | `Diode_SMD:D_SOD-323` or `Package_TO_SOT_SMD:SOT-23` | TVS |
| D6 | `Diode_SMD:D_SOD-123` | Flyback |
| D7 | `Diode_SMD:D_SMA` | Schottky |
| D8-D11 | `LED_SMD:LED_0805_2012Metric` | LEDs |
| C1 | `Capacitor_THT:CP_Radial_D8.0mm_P3.50mm` | 100uF/35V |
| C2 | `Capacitor_THT:CP_Radial_D6.3mm_P2.50mm` | 100uF/10V |
| C3-C6 | `Capacitor_SMD:C_0805_2012Metric` | 10uF |
| C7-C8 | `Capacitor_SMD:C_0603_1608Metric` | 100nF |
| R1-R13 | `Resistor_SMD:R_0603_1608Metric` | Various |
| F1 | `Fuse:Fuse_1812_4532Metric` | Polyfuse |
| H1-H4 | `MountingHole:MountingHole_2.7mm_M2.5` | M2.5 holes |

## Design Rules for Manufacturing

| Parameter | Value | JLCPCB Compatible |
|-----------|-------|-------------------|
| Min Track Width | 0.2mm (8mil) | Yes (min 0.127mm) |
| Min Clearance | 0.2mm | Yes (min 0.127mm) |
| Min Via Diameter | 0.5mm | Yes (min 0.45mm) |
| Min Via Drill | 0.3mm | Yes (min 0.2mm) |
| Min Hole Size | 0.3mm | Yes |
| Board Thickness | 1.6mm | Standard |
| Copper Weight | 1oz | Standard |

## Ordering from JLCPCB

1. Generate Gerber files from KiCad
2. Go to [jlcpcb.com](https://jlcpcb.com)
3. Upload Gerber ZIP file
4. Select options:
   - Layers: 2
   - Dimensions: 65 x 56.5 mm
   - PCB Thickness: 1.6mm
   - Solder Mask: Green (or your choice)
   - Silkscreen: White
   - Surface Finish: HASL (cheapest) or ENIG (better)

**Estimated cost:** $2-5 for 5 boards + shipping

## Assembly Options

### Self-Assembly
Order bare PCBs and solder components yourself.
Total BOM cost: ~$25-30 per board

### JLCPCB SMT Assembly
1. Generate BOM and CPL (Component Placement List) files
2. Upload with Gerbers
3. JLCPCB will solder SMD components
4. You solder through-hole parts (connectors, relay)

**Estimated cost:** ~$15-20 per board (qty 5) + component cost

## Files for Manufacturing

When ordering, you'll need:
- `gerbers/` - Gerber files (generate from KiCad)
- `pidoors-hat-bom.csv` - Bill of Materials
- `pidoors-hat-cpl.csv` - Component Placement List

## License

MIT License - See main project LICENSE file.

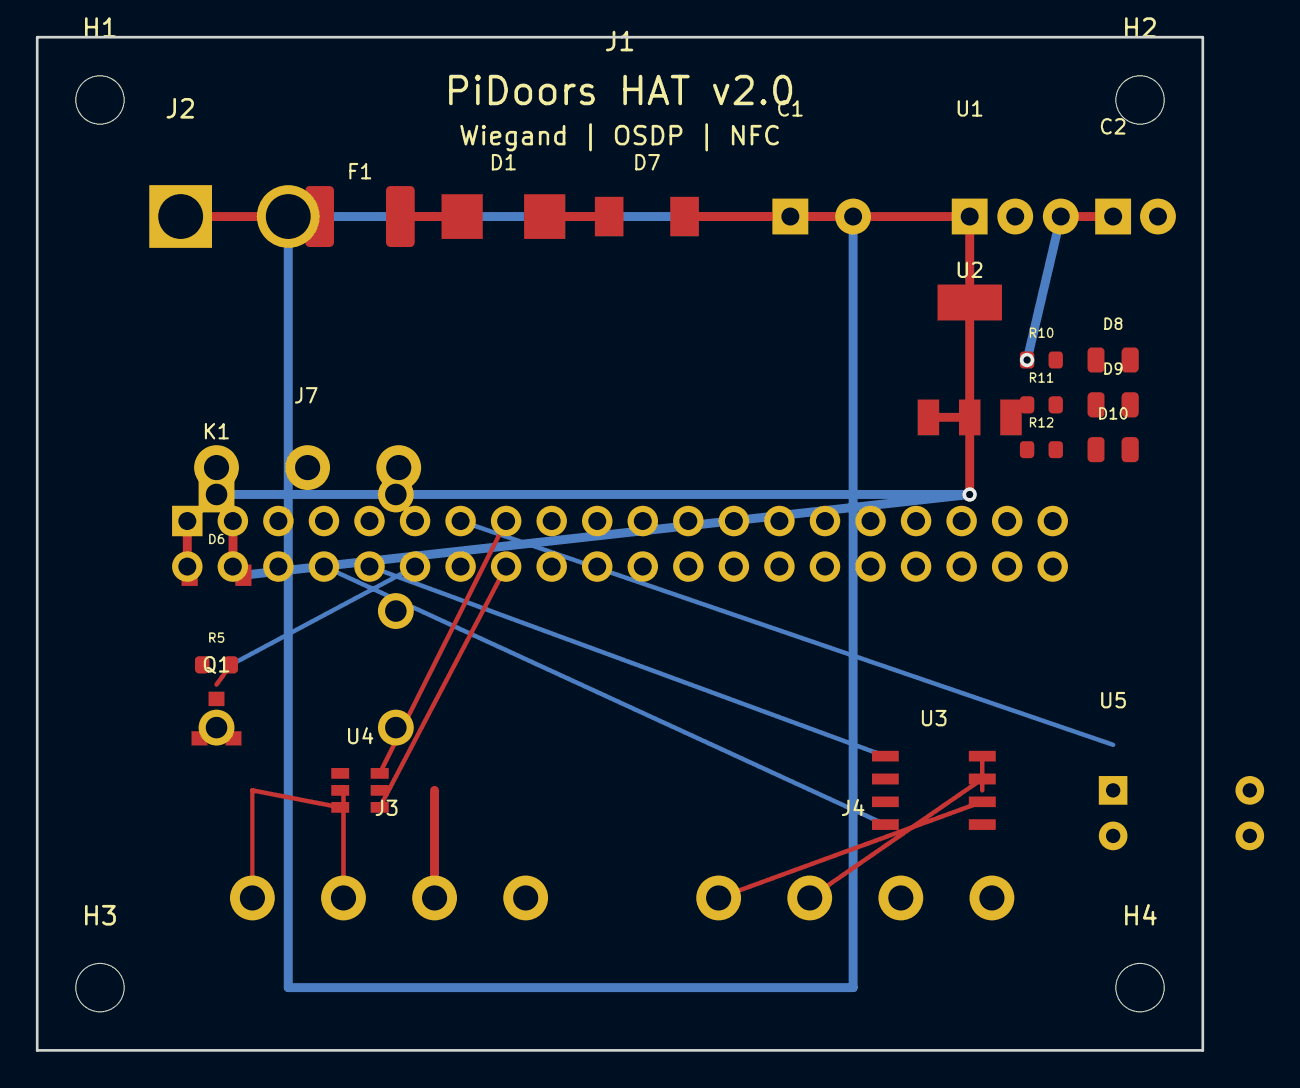
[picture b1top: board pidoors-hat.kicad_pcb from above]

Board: 2 copper layers, 65.0 x 56.5 mm, 29 parts (0 on the bottom side), 23 nets.

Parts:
C1: 100uF/35V; CP_Radial_D8.0mm_P3.50mm
C2: 100uF/10V; CP_Radial_D6.3mm_P2.50mm
D1: SMBJ24A; D_SMB
D6: 1N4148W; D_SOD-123
D7: SS34; D_SMA
D8: PWR; LED_0805_2012Metric
D9: OK; LED_0805_2012Metric
D10: ERR; LED_0805_2012Metric
F1: 1.1A; Fuse_1812_4532Metric
H1, H2, H3, H4: MountingHole; MountingHole_2.7mm_M2.5
J1: Raspberry_Pi; PinSocket_2x20_P2.54mm_Vertical
J2: 12V DC; BarrelJack_CUI_PJ-002A_Horizontal
J3: Wiegand; TerminalBlock_Phoenix_MKDS-1,5-4-5.08_1x04_P5.08mm_Horizont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
J4: RS485; TerminalBlock_Phoenix_MKDS-1,5-4-5.08_1x04_P5.08mm_Horizont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
J7: Relay_Out; TerminalBlock_Phoenix_MKDS-1,5-3-5.08_1x03_P5.08mm_Horizont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
K1: G5LE-14_DC12; Relay_SPDT_Omron-G5LE-14
Q1: MMBT2222A; SOT-23
R5, R10: 1k; R_0603_1608Metric
R11: 330; R_0603_1608Metric
R12: 220; R_0603_1608Metric
U1: OKI-78SR-5; Converter_DCDC_muRata_OKI-78SRx_Vertical
U2: LD1117S33; SOT-223-3_TabPin2
U3: MAX13487E; SOIC-8_3.9x4.9mm_P1.27mm
U4: TXB0102; SOT-23-6
U5: PC817; DIP-4_W7.62mm

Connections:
+3V3: J1.1, J1.17, U2.2, U2.4, U3.8, U4.1, U5.4
+5V: C2.1, D7.2, J1.2, J1.4, J3.3, R10.1, U1.3, U2.3, U4.2
+12V: F1.1, J2.1
+12V_FUSED: C1.1, D1.2, D6.2, D7.1, F1.2, K1.1, U1.1
GND: C1.2, C2.2, D1.1, D8.2, J1.6, J1.9, J1.14, J1.20, J1.25, J1.30, J1.34, J1.39, J2.2, J3.4, J4.3, Q1.3, U1.2, U2.1, U3.5
GPIO14_TX: J1.8, U3.4
GPIO15_RX: J1.10, U3.1
GPIO18_RELAY: J1.12, R5.1
GPIO22_LED_ERR: J1.15, R12.1
GPIO23_D1: J1.16, U4.6
GPIO24_D0: J1.18, U4.4
GPIO25_LED_OK: J1.22, R11.1
GPIO27_DOOR: J1.13, U5.3
LED_ERR_ANODE: D10.1, R12.2
LED_OK_ANODE: D9.1, R11.2
PWR_LED: D8.1, R10.2
RELAY_BASE: Q1.1, R5.2
RELAY_COIL: D6.1, K1.2, Q1.2
RELAY_COM: J7.2, K1.4
RELAY_NC: J7.3, K1.5
RELAY_NO: J7.1, K1.3
RS485_A: J4.1, U3.6
RS485_B: J4.2, U3.7

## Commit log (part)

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2021-03-14 ignore
2023-04-26 login admin@fake.com Password admin
2026-01-10 Documentation update
2026-01-10 Migrate to Nginx
    - Fix critical security issue: remove exposed credentials from config.json
    - Add config.json to .gitignore and create config.json.example template
    - Migrate from Apache to Nginx with PHP-FPM for improved performance
    - Create nginx/pidoors.conf with security headers and hardened configuration
    - Fix deprecated mime_content_type() using finfo class in importcards.php
    - Rewrite README.md with cleaner documentation and Nginx references
2026-01-10 Feature: Add multi-reader support and persistent master cards
    Expand card reader and card type support with modular reader architecture:
    Reader Modules:
    - Add reader abstraction layer with BaseReader class and ReaderFactory
    - Wiegand: Support all standard formats (26, 32, 34, 35, 36, 37, 48-bit)
    - OSDP: RS-485 encrypted reader support with AES-128 Secure Channel
    - NFC PN532: I2C/SPI NFC reader for Mifare cards
2026-01-10 PCB: Replace outdated gerbers with professional v2.0 specification
    Remove old KiCad gerber files (basic 2020 design) and replace with
    comprehensive PCB specification document for professional manufacturing.
    New PCB_SPECIFICATION.md includes:
    - Multi-reader support (Wiegand, OSDP RS-485, PN532, MFRC522)
    - Complete protection circuits (ESD, surge, overcurrent, reverse polarity)
    - Optically isolated door sensor input
2026-01-10 Fix thread safety in legacy Wiegand handling
    Add wiegand_lock to protect reader stream and timer access in the
    legacy Wiegand code path. The GPIO interrupt callbacks (data_pulse)
    could race with the timer thread (wiegand_stream_done), potentially
    corrupting the bit stream.
    Changes:
    - Add wiegand_lock for legacy Wiegand stream synchronization
2026-01-10 Update tests
    Add comprehensive tests for:
    - Debug mode toggle and output functions
    - Cache load/save with valid, expired, and corrupted files
    - Master card load/save operations
    - Legacy 26-bit and 34-bit Wiegand validation
    - Triple swipe door lock toggle functionality
2026-01-10 Docs: Update README for v2.2.1 with migration instructions
    - Bump version to 2.2.1
    - Add database migration section with instructions
    - Add v2.2.1 changelog entry documenting security fix
    - Update current version in roadmap
2026-02-28 Fix responsive layout and add Docker deployment support
    Rewrite sidebar/content layout to properly scale across screen sizes.
    Remove conflicting inline CSS from header.php, fix Bootstrap 5 class
    names (ml->ms), use fixed sidebar with explicit margin-left offset on
    main content. Add Docker Compose setup (MariaDB + PHP-FPM + Nginx)
    for development and testing.
2026-02-28 Docs: Update installation guide for v2.3.0
2026-02-28 Fix lgpio temp file issue: use RuntimeDirectory for writable workdir
    lgpio (used by rpi-lgpio on Debian 12+) creates notification pipe files
    in the working directory on import. When WorkingDirectory was /opt/pidoors
    the service user couldn't write there, causing startup failure.
    - systemd service: use RuntimeDirectory=pidoors with WorkingDirectory=/run/pidoors
    - pidoors.py: add /opt/pidoors to sys.path before importing RPi.GPIO so
    local imports (formats, readers) still resolve from the install dir
2026-02-28 Fix door IP showing 127.0.0.1: detect IP after network is ready
    get_local_ip() was called at module load time before the network was up
    at boot, causing it to fall back to 127.0.0.1 permanently. Now:
    - IP detection runs in initialize() after systemd network.target
    - Heartbeat loop retries detection if still 127.0.0.1
2026-03-01 Remove unused migrations
2026-03-03 Harden client updater and surface error details to web UI
    Client update script (pidoors-update.sh):
    - Pre-flight checks verify archive contents before stopping service
    - Tracks copy successes/failures, aborts if any copy fails
    - VERSION and DB only updated after all copies succeed
    - Always restarts service on failure so controller isn't left dead
    - Writes detailed error messages to DB (e.g. "failed: Could not
2026-03-04 Fix backup download and delete breaking page
    Download served garbled binary mixed with HTML because header.php already
    sent output before file headers. Delete caused white page for the same
    reason. Added output buffering so download can discard buffered HTML before
    sending the file, and delete now renders inline instead of redirecting.
2026-03-05 Add master card support to root pidoorserv/ (the files the updater deploys)
    The web UI updater copies from pidoorserv/ at the repo root, not
    pidoors/pidoorserv/. The root copies were missing all master card
    functionality (checkbox, INSERT/DELETE, badge, lookup).
    - cards.php: add master_card checkbox, POST processing, master_cards
    table INSERT on add, DELETE on card delete, Master badge in list
    - editcard.php: add master_card checkbox, lookup on load, sync
2026-03-05 Fix white-page bug on redirects and broken CSV exports
    Add ob_start() to header.php so header() redirects work from any page
    (14 files affected). Add ob_end_clean() to export_logs.php and
    export_report.php to discard buffered HTML before sending CSV data.
2026-03-05 Fix installation instructions in README
    - Add missing packages: php-curl, php-json, python3-dev, python3-venv, curl
    - Add remote DB user (pidoors@%) and bind-address note for door controllers
    - Add users table and audit_logs table creation to manual schema import
    - Add VERSION file copy to web deploy step
    - Fix door controller config example to use actual door name with all fields
    - Fix dead links to INSTALLATION_GUIDE.md (was in pidoors/ subdirectory)
2026-03-06 Add TLS encryption for database connections (v2.6.0)
    Encrypt all controller-to-server MySQL traffic with TLS to prevent
    credential sniffing and unauthorized database access on the network.
    - Centralize 6 duplicate pymysql.connect() calls into get_db_connection()
    helper with automatic TLS when ca.pem exists
    - Server install generates self-signed CA + server cert for MariaDB
    - Controller install auto-downloads CA cert from server via HTTP
2026-03-08 Fix missing door column migrations breaking edit/unlock on upgraded installs
    database_migration.sql was missing ALTER TABLE migrations for
    unlock_requested and poll_interval columns on the doors table.
    These existed in docker/init-db.sql but not in the upgrade script,
    causing editdoor.php UPDATE to throw PDOException, remote unlock
    to fail, and controller command poll to error continuously.
2026-03-09 v2.6.5 — Security audit, bug fixes, Docker controller files
    Security:
    - Enforce require_admin() on all management pages (cards, doors, schedules,
    groups, holidays, logs, reports, exports)
    - Block deactivated users from logging in (check active flag)
    - Add HttpOnly, SameSite, Secure flags to session cookies
    - Delete .remote credential file, add .dockerignore
2026-03-09 v2.6.10 — Dashboard quick-unlock buttons
    - Add remote unlock button to each online door in the dashboard Door
    Status panel — small icon button, AJAX-powered, no page reload
    - Unlock action confirms before sending, briefly highlights on success
    - Works with live-updating content via delegated event handlers
2026-03-09 v2.6.12 — Fix real-time polling and dashboard unlock
    - Fix jQuery loading order bug that broke all AJAX polling on dashboard
    and logs pages (scripts ran before jQuery was loaded by footer.php)
    - Dashboard door panel: horizontal layout with colored lock badges
    - Unlock button shows "Unlocking" state immediately, hides until confirmed
    - 2-second polling across all pages for near real-time updates
2026-03-10 v2.17.1 — Controller updates now run database migrations
    Controller update script (pidoors-update.sh) now executes
    database_migration.sql after copying files, preventing doors from
    going offline when new code references columns that don't exist yet.
    Also synced root database_migration.sql which was missing the
    held_open/hold_requested column migrations from v2.17.0.
2026-03-10 v3.0.2 — Fix v2.x to v3.x upgrade path
    - Bundle pidoors-ui-dist/ inside pidoorserv/ in release tarballs so
    old v2.x updaters (which only copy pidoorserv/*) also copy the SPA
    - Add post-upgrade auto-deploy: update.php detects bundled SPA dist
    on first page load after upgrade and deploys it automatically
    - Clean up bundled dist from web root after deployment
2026-03-10 Fix VERSION path in auth/me endpoint (footer showed 'vunknown')
    Same ../VERSION bug as update/status — was reading /var/www/VERSION
    instead of /var/www/pidoors/VERSION.
2026-03-10 v3.0.5 — Fix card_id hex string handling throughout API
    card_id is a hex string (Wiegand raw value) stored as varchar(32),
    but the API was casting it to (int) on every lookup, breaking GET/PUT/
    DELETE for all real card readers. Removed all (int) casts on card_id,
    updated frontend types to string, and card creation now generates a
    card_id like the legacy PHP UI did.
2026-03-11 Fix push.php parse error — restore array_merge for string-keyed array
    The blanket replace_all of array_merge also hit the ping_controller
    return line which uses array_merge with string keys (correctly).
    Restored that call while keeping the CURLOPT fixes using + operator.
2026-03-12 Replace Docker setup with 2 minimal Bookworm containers
    Tear down the old 5-container setup (db, php, web, gateway, controller)
    and replace with just 2 debian:bookworm containers that mirror a real
    Raspberry Pi OS install:
    - server: MariaDB + PHP-FPM + Nginx all-in-one (mirrors install.sh option 1)
    - door: Mock door controller with pymysql/mock GPIO (mirrors install.sh option 2)
    Entrypoint scripts replicate install.sh logic step-by-step with comments
2026-03-14 v3.1.5 — Fix updater deleting ca.pem, auto-restore on update
    Server updater orphan cleanup was deleting ca.pem from web root on
    every update, breaking TLS verification for push pings and door
    controller DB connections. Now excluded from cleanup and auto-restored
    from /etc/mysql/ssl/ if missing.
2026-04-05 v3.1.9 — Update script self-detaches from service cgroup
    The update script now detects if it's running inside the
    pidoors.service cgroup and re-launches itself as an independent
    systemd transient service before proceeding. This ensures the
    update survives systemctl stop pidoors regardless of how it was
    launched (push, heartbeat, or manual).
    Also patches older release scripts during self-update to inject
2026-04-05 Fix systemd-run unit name collision and self-detach loop
    Use timestamp-based unit names for systemd-run transient services
    to avoid "unit already loaded" errors on repeated updates. Fix
    self-detach cgroup pattern to exclude pidoors-update services so
    the script doesn't try to detach from itself.
2026-04-11 Fix status LED pin selector type error
2026-04-11 v0.3.8 — Auto-close, dashboard gate controls, session fix
    Gate auto-close:
    - New optional clearance sensor input (4th gate input) for beam-break,
    IR, or laser sensors at the gate opening
    - Configurable polarity and "active means clear/blocked" logic
    - New auto_close section in gate config: enable + delay (1-3600s)
    - Mandatory safety: auto-close requires a clearance sensor — UI greys

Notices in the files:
README.md:
License: Open Source
